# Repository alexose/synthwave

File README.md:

# Synthwave

An open-source experiment in carbon removal based on the electrochemical pH swing of seawater.

Developed by Alex Ose with input from many wonderful collaborators via the
[OpenAir Collective](https://openaircollective.cc/).

-   [OpenAir Forums](https://www.openairforum.org/t/introducing-synthwave/806)
-   [OpenAir Discord](https://openaircollective.cc/join)

## Introduction

Synthwave demonstrates the removal of CO2 from seawater using
[a technique developed by the Alan Hatton lab at MIT](https://pubs.rsc.org/en/content/articlelanding/2023/EE/d2ee03804h)
using a 3D printed shell and common, off-the-shelf components. With a materials list under $300, Synthwave is designed
to be an entry point for anyone looking to learn more about ocean-based carbon capture.

It is designed to be fully hackable, with an emphasis on approachability. Our goal is to bring ocean-based
electrochemical capture to a wider audience!

## Hardware

### Moving parts

The hardware is based around cheap 12V devices (that can easily be sourced from Amazon or eBay) controlled by a common
ESP32 microcontroller. The full list of materials can be found [here](MATERIALS.md).

### 3D printed parts

Each of the above parts are mounted onto a 3D printed frame that can be found in the `/model` directory of this repo.
Because it is designed to sit on top of a standard 5-gallon bucket, printing this frame requires a large-format printer
with a build area of at least 320x320mm.

There are several parts:

-   Base
-   Container cover
-   Back cover (optional)
-   Two pump brackets
-   Two strain relief brackets
-   Two electrode holders

Please refer to the README.md inside of the `/model` directory for pointers on how to print and assemble the device.

### Electrodes

As this is an electrochemistry project, it requires electrodes. While the exact formulation of these are under active
development, I would be happy to send you a working set of electrodes for free. Please get in touch with me directly in
order to arrange this.

Should you choose to develop your own electrodes, please consult
[this thread in the OpenAir forums](https://www.openairforum.org/t/synthwave-electrochemical-co2-capture-from-seawater/781/4)
for more information.

## Software

The software that controls this system is designed to be as readable as possible. It uses Arduino-compatible code to
connect to a local WiFi network and expose a simple API. This API accepts various parameters that allow a client to
toggle each individual pump, solenoid, and/or electrode set.

This allows us to control the system entirely from a web browser, which allows easy fine-tuning of process variables
without the need to continuously re-flash the ESP32 server.

Should you need to re-flash the ESP32, this can be accomplished via the /update endpoint. The software uses the
[ElegantOTA](https://github.com/ayushsharma82/ElegantOTA) library to allow for simple, over-the-air reflashing as to not
require a physical connection to the device.

## System modeling

Our current estimates show that Synthwave removes about of 0.076g of CO2 per run cycle[1]. Assuming a cycle time of five
minutes, an unlimited source of seawater, and non-degrading electrodes, it should be able to remove 22g of CO2 per day.

There are many, many variables that will affect this final number: The quality of the electrodes, the concentration of
CO2 in the seawater, the cycle frequency, and the efficiency of our electrochemical reaction.

Above all else, Synthwave aims to put our assumptions to the test, and help inform our next phase of research.

[1]: The original paper cites 0.0543 mmol of CO2 removed per cycle, with water volumes of about 30mL. Scaling this up to
1L gives us 1.7404 mmol, or 0.0766 grams of CO2.

## Future research

Synthwave is designed to be a simple demonstration of a specific carbon capture technique. In order to achieve
commercial viability, virtually all aspects of this technique will need to be improved.

The main need is to improve the quality of our electrodes. This will likely involve better coating techniques to avoid
degredation and fouling, as well as more accurate measurements, CV charts, etc.

With improved electrodes, the next step would be to improve the throughput of the device to handle much more seawater.
This could be achieved by increasing the size of the system, designing a more efficient cell (ideally a flow cell), or
perhaps building multiple machines to work in parallel with one another.

We hope that by publishing this work under the CERN license, future hackers and collaborators will share their
learnings. It is only by the overwhelming success of carbon capture do we hope to maintain a livable climate. By
investing your time and energy in projects like this one, we may uncover key techniques that make gigaton-scale carbon
capture viable.

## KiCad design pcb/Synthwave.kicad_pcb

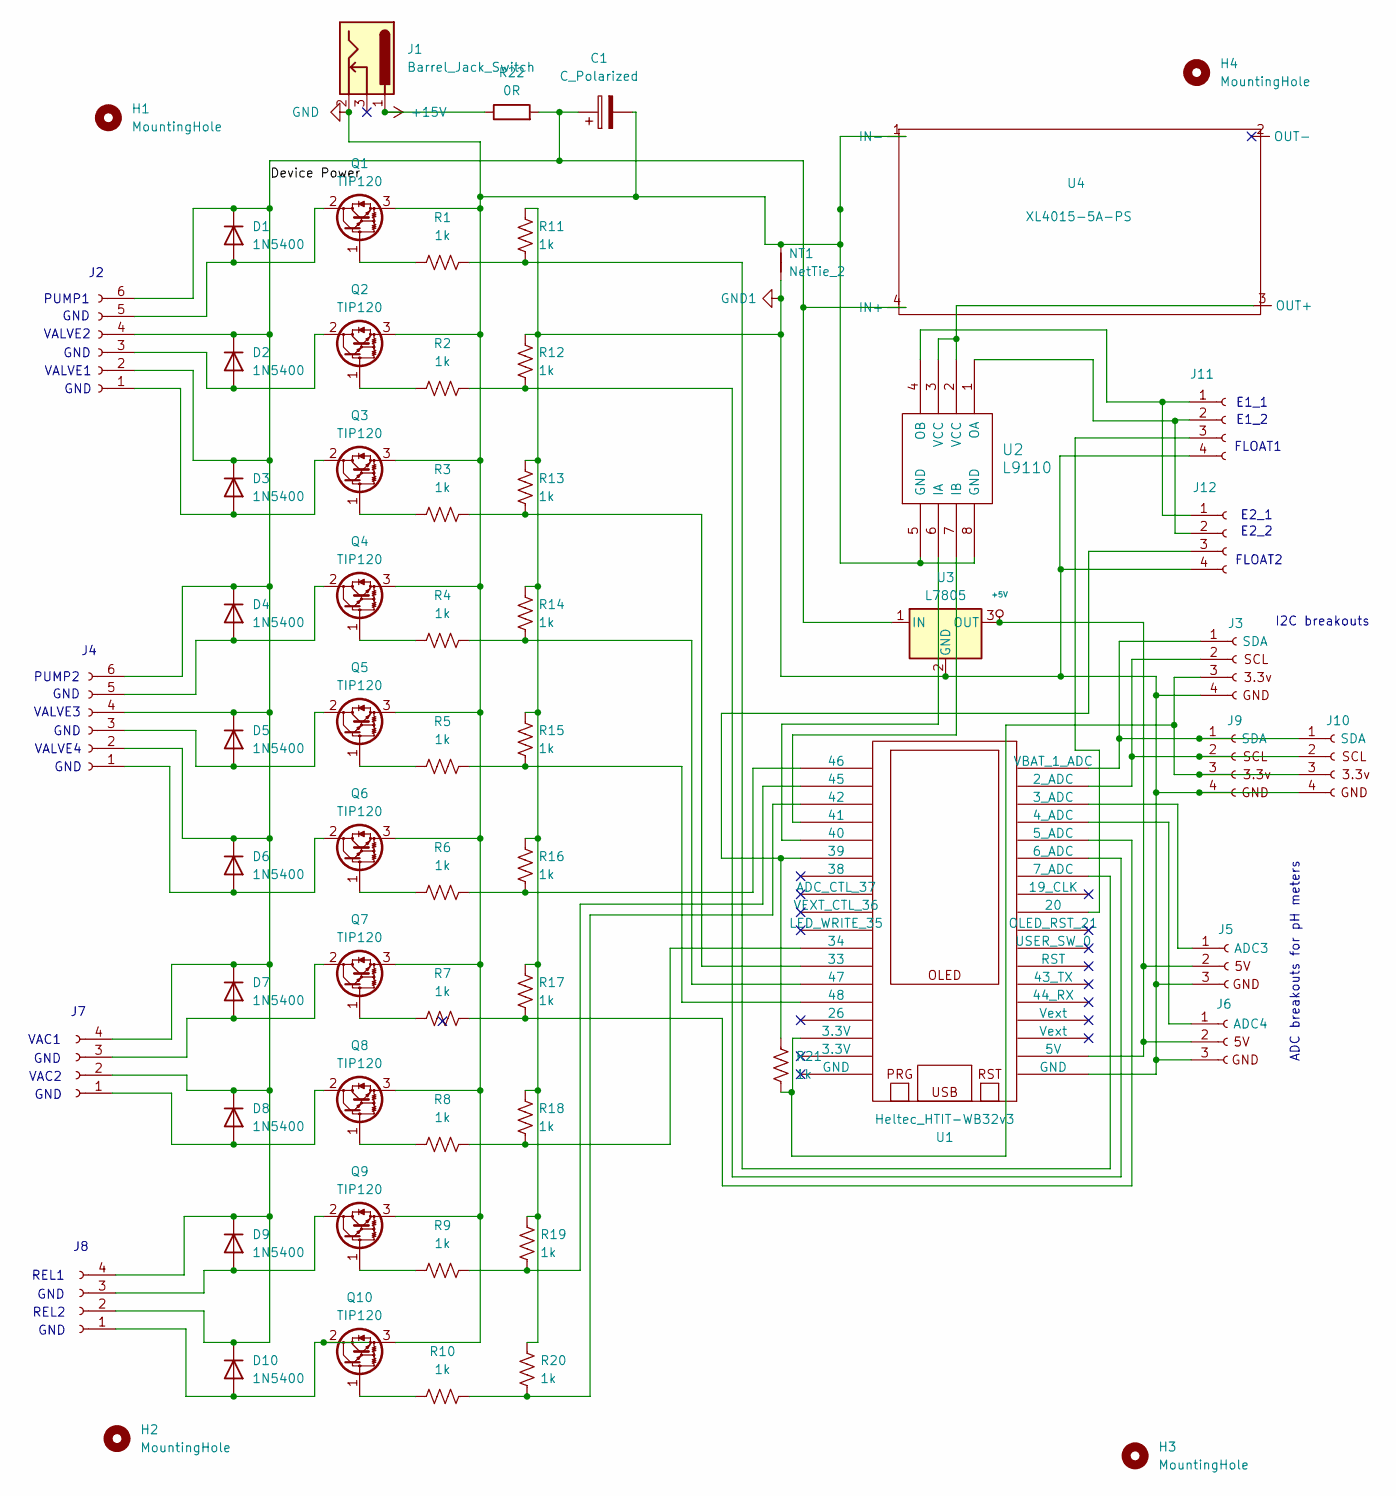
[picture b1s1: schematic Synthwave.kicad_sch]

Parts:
C1: C_Polarized; CP_Radial_D7.5mm_P2.50mm
D1, D2, D3, D4, D5, D6, D7, D8, D9, D10: 1N5400; D_DO-34_SOD68_P10.16mm_Horizontal
H1, H2, H3, H4: MountingHole; MountingHole_2.2mm_M2
J1: Barrel_Jack_Switch; BarrelJack_Horizontal
J2, J4: Conn_01x06_Socket; JST_XH_S6B-XH-A_1x06_P2.50mm_Horizontal
J3, J9, J10: SDA; JST_XH_S4B-XH-A_1x04_P2.50mm_Horizontal
J5: ADC3; PinHeader_1x03_P2.54mm_Vertical
J6: ADC4; PinHeader_1x03_P2.54mm_Vertical
J7, J8, J12: Conn_01x04_Socket; JST_XH_S4B-XH-A_1x04_P2.50mm_Horizontal
J11: ELEC1 FLOAT1; JST_XH_S4B-XH-A_1x04_P2.50mm_Horizontal
NT1: NetTie_2; PinHeader_1x02_P2.54mm_Vertical
Q1, Q2, Q3, Q4, Q5, Q6, Q7, Q8, Q9, Q10: TIP120; TO-220-3_Vertical
R1, R2, R3, R4, R5, R6, R7, R8, R9, R10, R11, R12, R13, R14, R15, R16, R17, R18, R19, R20, R21: 1k; R_Axial_DIN0207_L6.3mm_D2.5mm_P7.62mm_Horizontal
R22: 0R; PinHeader_1x02_P2.54mm_Vertical
U1: Heltec_HTIT-WB32v3; Heltec_HTIT-WB32
U2: L9110; DIP-8_W7.62mm
U3: L7805; TO-220-3_Vertical
U4: XL4015-5A-PS

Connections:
+5V: J5.2, J6.2, U1.9 (5V), U3.3 (OUT)
+15V: J1.1, R22.1
/Device Power: C1.1, D1.1 (K), D2.1 (K), D3.1 (K), D4.1 (K), D5.1 (K), D6.1 (K), D7.1 (K), D8.1 (K), D9.1 (K), D10.1 (K), J2.2, J2.4, J2.6, J4.2, J4.4, J4.6, J7.2, J7.4, J8.2, J8.4, R22.2, U3.1 (IN), U4.4 (IN+)
GND: C1.2, J1.2, NT1.2, Q1.3 (E), Q2.3 (E), Q3.3 (E), Q4.3 (E), Q5.3 (E), Q6.3 (E), Q7.3 (E), Q8.3 (E), Q9.3 (E), Q10.3 (E), U2.5 (GND), U2.8 (GND), U4.1 (IN-)
GND1: J3.4, J5.3 (PIN), J6.3 (PIN), J9.4, J10.4, J11.4, J12.4, NT1.1, R11.2, R12.2, R13.2, R14.2, R15.2, R16.2, R17.2, R18.2, R19.2, R20.2, U1.8 (GND), U3.2 (GND)
unnamed: D1.2 (A), J2.5, Q1.2 (C)
unnamed: D2.2 (A), J2.3, Q2.2 (C)
unnamed: D3.2 (A), J2.1, Q3.2 (C)
unnamed: D4.2 (A), J4.5, Q4.2 (C)
unnamed: D5.2 (A), J4.3, Q5.2 (C)
unnamed: D6.2 (A), J4.1, Q6.2 (C)
unnamed: D7.2 (A), J7.3, Q7.2 (C)
unnamed: D8.2 (A), J7.1, Q8.2 (C)
unnamed: D9.2 (A), J8.3, Q9.2 (C)
unnamed: D10.2 (A), J8.1, Q10.2 (C)
unnamed: J5.1, U1.38 (3_ADC)
unnamed: J6.1, U1.39 (4_ADC)
unnamed: J3.1, J9.1, J10.1, U1.36 (VBAT_1_ADC)
unnamed: J3.2, J9.2, J10.2, U1.37 (2_ADC)
unnamed: J3.3, J9.3, J10.3, R21.1, U1.11 (3.3V)
unnamed: J11.1, J12.1, U2.4 (OB)
unnamed: J11.2, J12.2, U2.1 (OA)
unnamed: J11.3, U1.25 (20)
unnamed: J12.3, R21.2, U1.5 (39)
unnamed: Q1.1 (B), R1.1
unnamed: Q2.1 (B), R2.1
unnamed: Q3.1 (B), R3.1
unnamed: Q4.1 (B), R4.1
unnamed: Q5.1 (B), R5.1
unnamed: Q6.1 (B), R6.1
unnamed: Q7.1 (B), R7.1
unnamed: Q8.1 (B), R8.1
unnamed: Q9.1 (B), R9.1
unnamed: Q10.1 (B), R10.1
unnamed: R7.2, R17.1, U1.34 (5_ADC)
unnamed: R2.2, R12.1, U1.35 (6_ADC)
unnamed: R1.2, R11.1, U1.32 (7_ADC)
unnamed: R3.2, R13.1, U1.15 (33)
unnamed: R8.2, R18.1, U1.2 (34)
unnamed: U1.18 (40), U2.6 (IA)
unnamed: U1.23 (41), U2.7 (IB)
unnamed: R10.2, R20.1, U1.19 (42)
unnamed: R9.2, R19.1, U1.22 (45)
unnamed: R6.2, R16.1, U1.21 (46)
unnamed: R4.2, R14.1, U1.3 (47)
unnamed: R5.2, R15.1, U1.1 (48)
unnamed: U2.2 (VCC), U2.3 (VCC), U4.3 (OUT+)

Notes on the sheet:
E1_1
REL2
VAC2
PUMP2
E2_2
FLOAT2
GND
VALVE4
E2_1
FLOAT1
VAC1
ADC breakouts for pH meters
VALVE3
VALVE2
VALVE1
PUMP1
I2C breakouts
E1_2
REL1

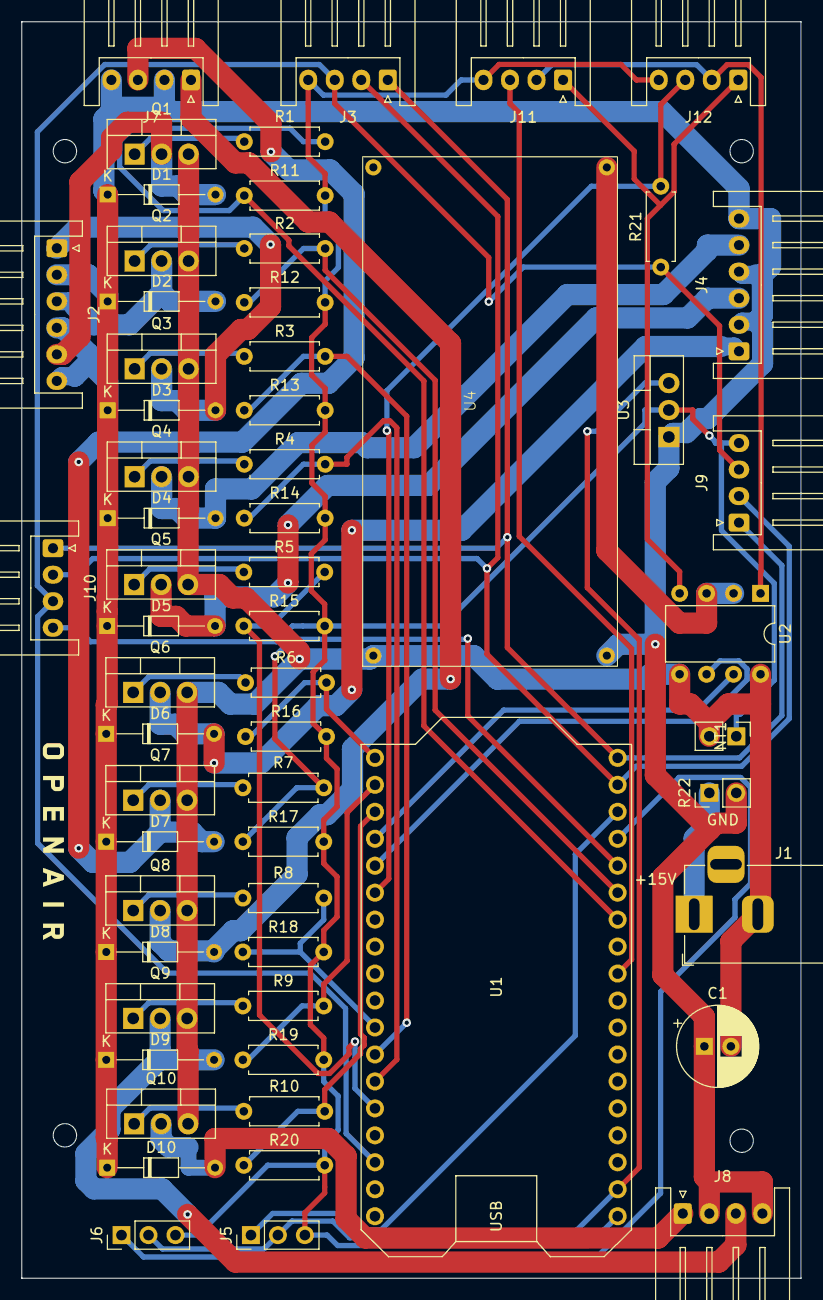
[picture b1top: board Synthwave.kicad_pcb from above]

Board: 2 copper layers, 73.4 x 118.4 mm, 64 parts (0 on the bottom side), 47 nets.

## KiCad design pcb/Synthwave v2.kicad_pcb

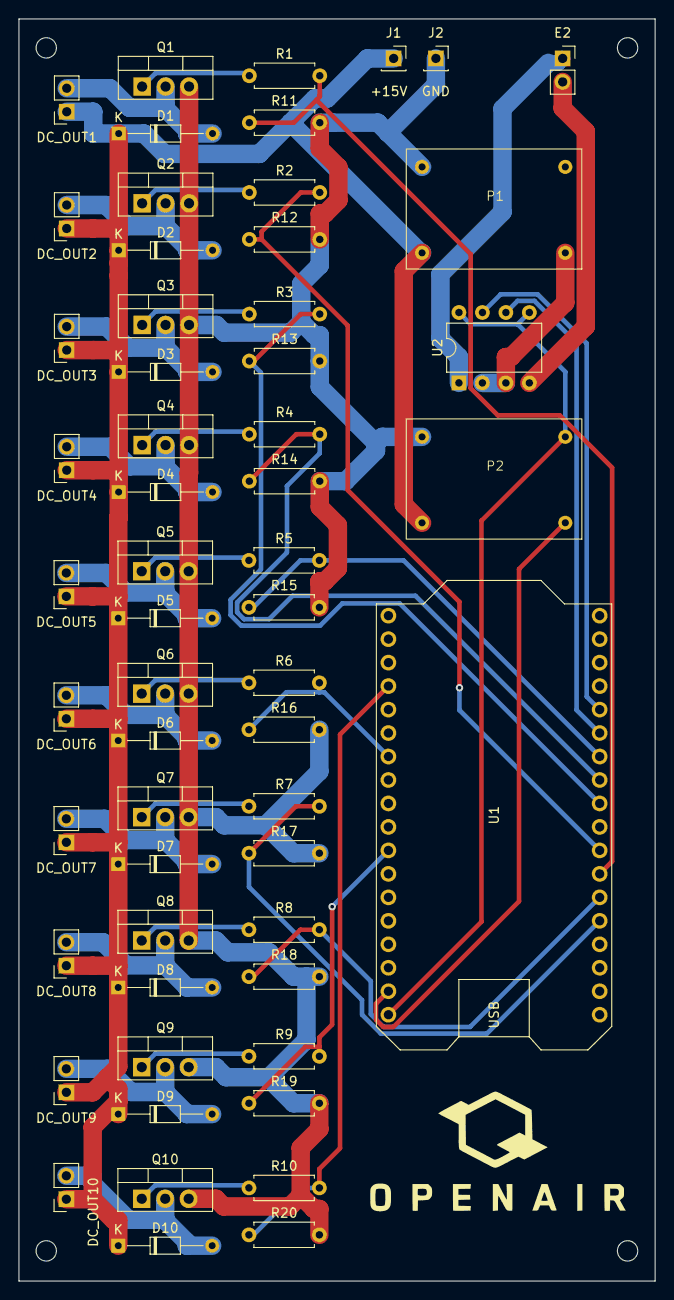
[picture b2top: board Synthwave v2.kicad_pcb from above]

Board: 2 copper layers, 68.8 x 136.6 mm, 61 parts (0 on the bottom side), 39 nets.

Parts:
D1, D2, D3, D4, D5, D6, D7, D8, D9, D10: 1N5400; D_DO-34_SOD68_P10.16mm_Horizontal
DC_OUT1, DC_OUT2, DC_OUT3, DC_OUT4, DC_OUT5, DC_OUT6, DC_OUT7, DC_OUT8, DC_OUT9, DC_OUT10: GND; PinSocket_1x02_P2.54mm_Vertical
E2: E1; PinSocket_1x02_P2.54mm_Vertical
H1, H2, H3, H4: MountingHole; MountingHole_2.2mm_M2
J1, J2: Conn_01x01_Pin; PinSocket_1x01_P2.54mm_Vertical
P1, P2: MINI-360
Q1, Q2, Q3, Q4, Q5, Q6, Q7, Q8, Q9, Q10: TIP120; TO-220-3_Vertical
R1, R2, R3, R4, R5, R6, R7, R8, R9, R10, R11, R12, R13, R14, R15, R16, R17, R18, R19, R20: 1k; R_Axial_DIN0207_L6.3mm_D2.5mm_P7.62mm_Horizontal
U1: Heltec_HTIT-WB32
U2: L9110; DIP-8_W7.62mm

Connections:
+15V: D1.1 (K), D2.1 (K), D3.1 (K), D4.1 (K), D5.1 (K), D6.1 (K), D7.1 (K), D8.1 (K), D9.1 (K), D10.1 (K), DC_OUT1.1, DC_OUT2.1, DC_OUT3.1, DC_OUT4.1, DC_OUT5.1, DC_OUT6.1, DC_OUT7.1, DC_OUT8.1, DC_OUT9.1, DC_OUT10.1, J1.1, P1.4 (IN+), P2.4 (IN+)
GND: J2.1, P1.1 (IN-), P2.1 (IN-), Q1.3 (E), Q2.3 (E), Q3.3 (E), Q4.3 (E), Q5.3 (E), Q6.3 (E), Q7.3 (E), Q8.3 (E), Q9.3 (E), Q10.3 (E), R11.2, R12.2, R13.2, R14.2, R15.2, R16.2, R17.2, R18.2, R19.2, R20.2
unnamed: D1.2 (A), DC_OUT1.2, Q1.2 (C)
unnamed: D2.2 (A), DC_OUT2.2, Q2.2 (C)
unnamed: D3.2 (A), DC_OUT3.2, Q3.2 (C)
unnamed: D4.2 (A), DC_OUT4.2, Q4.2 (C)
unnamed: D5.2 (A), DC_OUT5.2, Q5.2 (C)
unnamed: D6.2 (A), DC_OUT6.2, Q6.2 (C)
unnamed: D7.2 (A), DC_OUT7.2, Q7.2 (C)
unnamed: D8.2 (A), DC_OUT8.2, Q8.2 (C)
unnamed: D9.2 (A), DC_OUT9.2, Q9.2 (C)
unnamed: D10.2 (A), DC_OUT10.2, Q10.2 (C)
unnamed: E2.1, U2.1 (OA)
unnamed: E2.2, U2.4 (OB)
unnamed: P1.3 (OUT+), U2.2 (VCC), U2.3 (VCC)
unnamed: P2.3 (OUT+), U1.20 (5V)
unnamed: P2.2 (OUT-), U1.28 (GND), U2.5 (GND), U2.8 (GND)
unnamed: Q1.1 (B), R1.1
unnamed: Q2.1 (B), R2.1
unnamed: Q3.1 (B), R3.1
unnamed: Q4.1 (B), R4.1
unnamed: Q5.1 (B), R5.1
unnamed: Q6.1 (B), R6.1
unnamed: Q7.1 (B), R7.1
unnamed: Q8.1 (B), R8.1
unnamed: Q9.1 (B), R9.1
unnamed: Q10.1 (B), R10.1
unnamed: R1.2, R11.1, U1.14
unnamed: R10.2, R20.1, U1.23
unnamed: R2.2, R12.1, U1.27
unnamed: R4.2, R14.1, U1.33
unnamed: R5.2, R15.1, U1.32
unnamed: R6.2, R16.1, U1.17
unnamed: R7.2, R17.1, U1.13
unnamed: R8.2, R18.1, U1.12
unnamed: R9.2, R19.1, U1.2
unnamed: R3.2, R13.1, U1.25 (25_DAC)
unnamed: U1.35, U2.6 (IA)
unnamed: U1.34, U2.7 (IB)

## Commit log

2023-09-01 Add 3d printing files
2023-09-07 Rename and move files
2023-10-26 Add LICENSE.txt
2023-10-26 Minor updates
2023-10-26 Add citation.cff
2023-10-26 Update orcid
2023-11-11 Fit improvements
2023-11-15 Add makefile, improve design
2023-11-15 Add image
2023-11-15 Improve sleekness
2023-11-18 Move holes forward for easier tube routing
2023-11-30 Add standoffs for PCB
2023-11-30 Add pcb prototype design
2023-11-30 Update gpio pins
2023-11-30 Update scad file
2023-11-30 remove unneeded file
2023-11-30 Rename files
2023-12-03 Many small updates
2023-12-03 Small edition
2023-12-03 Update and upgrades
2023-12-07 Fix typo in makefile
2023-12-15 Add model updates and various files
2023-12-16 Add List of Materials
2023-12-16 Update total price
2023-12-16 Update MATERIALS
2023-12-16 Fix broken link
2023-12-16 Bug fixes
2023-12-17 Update link to materials
2023-12-17 Update ardiuno code + binaries
2023-12-19 Add DOI
2023-12-23 Work on back cover
2023-12-23 Various updates
2023-12-23 Update makefile and remove top shelf
2023-12-23 Update software for routines
2023-12-23 Add scaffold for taking measurements via influxdb
2024-01-08 Basic intro to client
2024-01-08 Remove extra spiffs.bin
2024-01-08 Update system estimates
2024-01-18 Remove unnneeded files
2024-01-22 Work on routines
2024-01-22 Add TODO for pcb
2024-01-28 Further work on routines. Reading of pH sensor ADC pins.
2024-01-28 Add timestamp. Improve other various abilities.
2024-01-28 Experimenting with modbus SCD30
2024-01-29 Updates to arduino files. Add ink spreader model
2024-01-29 Add electrodes guide
2024-01-29 Remove like so
2024-01-29 Fix typo
2024-02-01 Update electrode information, many small tweaks
2024-02-05 Add lots and lots of connectors to PCB
2024-02-05 PCB updates
2024-02-07 Upgrade to elegantota 3.0
2024-02-07 Last minute modifications to v1
2024-02-07 Put CO2 readings into client
2024-02-07 redesign electrode holder
2024-02-07 Start on container cover redesign
2024-02-07 Switch to better buck converter board
2024-02-07 Combine JST connectors
2024-02-07 rerender model
2024-02-08 Update electrode holder
2024-02-08 Update images
2024-02-09 Rebuild model
2024-02-12 Add files via upload
    Added OSHWA UID certification mark. (OSHWA UID US002582)
2024-02-12 Update README.md
    Added OSHWA link
2024-02-14 Finish autorouting. Updates to electrode holder and container cover
2024-02-16 Model updaets
2024-03-02 Give containers a little more breathing room
2024-03-02 Update materials list
